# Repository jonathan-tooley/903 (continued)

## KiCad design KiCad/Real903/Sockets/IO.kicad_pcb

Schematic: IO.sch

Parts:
J3: IDC-Header_2x03_P2.54mm_Vertical
JSKT4: Circ61; MC61
JSKT4-1, JSKT4-2, JSKT4-3: IDC-Header_2x10_P2.54mm_Vertical
JSKT13: Circ19; MC19

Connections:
/Control Unit/0v: J3.5, J3.6, JSKT4.A, JSKT13.B, JSKT13.D, JSKT13.F, JSKT13.H, JSKT13.K, JSKT13.M, JSKT13.P, JSKT13.S, JSKT13.U
/Control Unit/+6v: J3.4, JSKT4.~p~
/IO/BT-30-U: JSKT4-2.17, JSKT13.N
/IO/IG1: JSKT4.~q~, JSKT4-3.1
/IO/IG2: JSKT4.~r~, JSKT4-3.2
/IO/IG3: JSKT4.~s~, JSKT4-3.3
/IO/IG4: JSKT4.~t~, JSKT4-3.4
/IO/IG5: JSKT4.~u~, JSKT4-3.5
/IO/IG6: JSKT4.~v~, JSKT4-3.6
/IO/IG7: JSKT4.~w~, JSKT4-3.7
/IO/IG8: JSKT4.~x~, JSKT4-3.8
/IO/IG9: JSKT4.~y~, JSKT4-3.9
/IO/IG10: JSKT4.~z~, JSKT4-3.10
/IO/IG11: JSKT4.AA, JSKT4-3.11
/IO/IG12: JSKT4.BB, JSKT4-3.12
/IO/IG13: JSKT4.CC, JSKT4-3.13
/IO/IG14: JSKT4.DD, JSKT4-3.14
/IO/IG15: JSKT4.EE, JSKT4-3.15
/IO/IG16: JSKT4.FF, JSKT4-3.16
/IO/IG17: JSKT4.GG, JSKT4-3.17
/IO/IG18: JSKT4.HH, JSKT4-3.18
/IO/LW-30-13: JSKT4-2.18, JSKT13.R
/IO/OA1: JSKT4.B, JSKT4-1.1
/IO/OA2: JSKT4.C, JSKT4-1.2
/IO/OA3: JSKT4.D, JSKT4-1.3
/IO/OA4: JSKT4.E, JSKT4-1.4
/IO/OA5: JSKT4.F, JSKT4-1.5
/IO/OA6: JSKT4.G, JSKT4-1.6
/IO/OA7: JSKT4.H, JSKT4-1.7
/IO/OA8: JSKT4.J, JSKT4-1.8
/IO/OA9: JSKT4.K, JSKT4-1.9
/IO/OA10: JSKT4.L, JSKT4-1.10
/IO/OA11: JSKT4.M, JSKT4-1.11
/IO/OA12: JSKT4.N, JSKT4-1.12
/IO/OA13: JSKT4.P, JSKT4-1.13
/IO/OA14: JSKT4.R, JSKT4-1.14
/IO/OA15: JSKT4.S, JSKT4-1.15
/IO/OA16: JSKT4.T, JSKT4-1.16
/IO/OA17: JSKT4.U, JSKT4-1.17
/IO/OA18: JSKT4.V, JSKT4-1.18
/IO/OS1: JSKT4.W, JSKT4-1.19
/IO/OS2: JSKT4.X, JSKT4-1.20
/IO/OS3: JSKT4.Y, JSKT4-2.1
/IO/OS4: JSKT4.Z, JSKT4-2.2
/IO/OS5: JSKT4.~a~, JSKT4-2.3
/IO/OS6: JSKT4.~b~, JSKT4-2.4
/IO/OS7~: JSKT4.~c~, JSKT4-2.5
/IO/OS8: JSKT4.~d~, JSKT4-2.6
/IO/OS9: JSKT4.~e~, JSKT4-2.7
/IO/OS10: JSKT4.~f~, JSKT4-2.8
/IO/OS11: JSKT4.~g~, JSKT4-2.9
/IO/PI1-29-AE: JSKT4-2.11, JSKT13.A
/IO/PI2-29-AF: JSKT4-2.12, JSKT13.C
/IO/PI3-29-AH: JSKT4-2.13, JSKT13.E
/IO/PR-30-E: JSKT4-2.16, JSKT13.L
/IO/PUNCH-INT: J3.3, JSKT13.T
/IO/RDR-INT: J3.1, JSKT13.V
/IO/RESET-32-20: JSKT4.PP, JSKT4-3.20
/IO/SIP-30-21: JSKT4-2.15, JSKT13.J
/IO/SOP-30-20: JSKT4-2.14, JSKT13.G
GND: J3.2, JSKT4.LL

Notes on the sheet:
Input/Output Control
Input/Output Data
OA Data
IG Data
OS Data
BP3

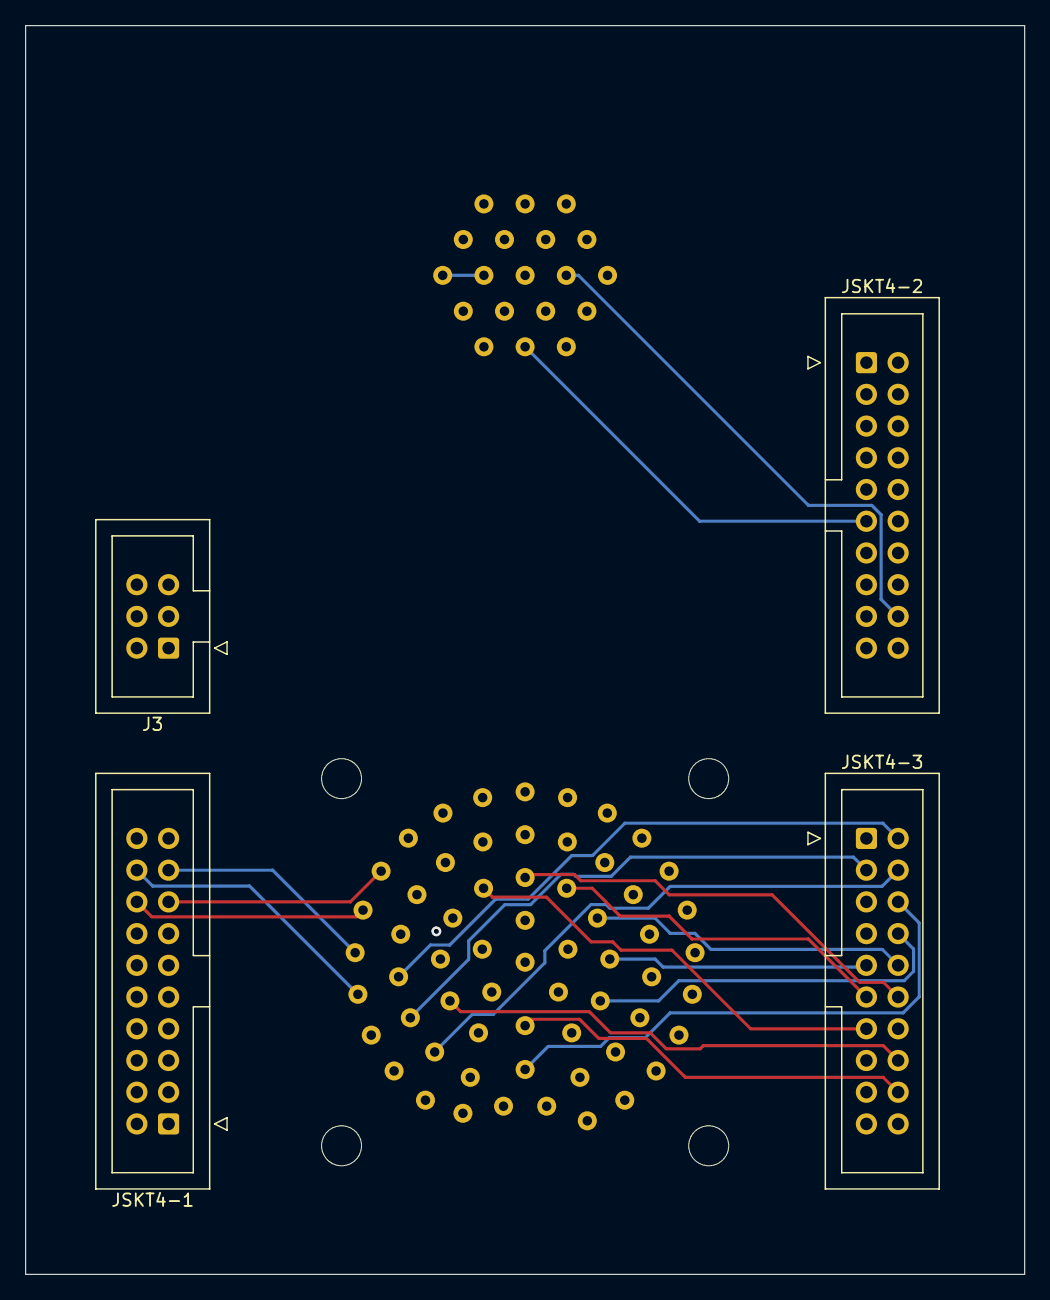
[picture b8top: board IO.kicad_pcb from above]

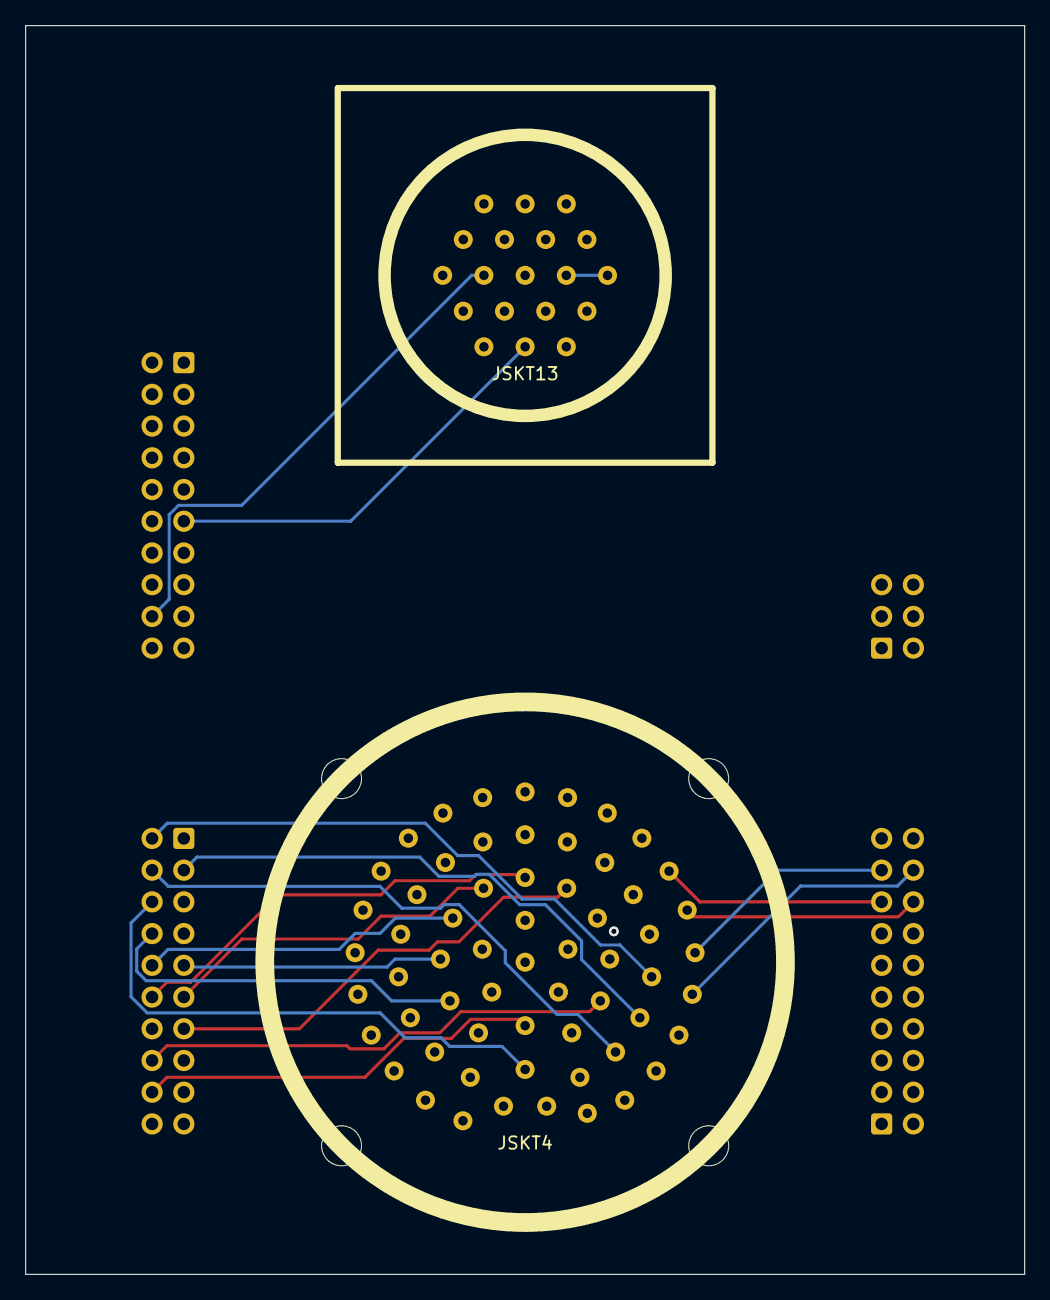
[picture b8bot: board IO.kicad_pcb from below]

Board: 4 copper layers, 80.0 x 100.0 mm, 6 parts (2 on the bottom side), 61 nets.

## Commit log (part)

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2017-02-05 Set up the project on Monodevelop
2017-02-08 Test
2017-04-22 23 April
2017-04-29 Start work on building console
2017-04-30 Added U2 input handling
2017-05-10 Removed gui file
2017-05-10 Fix to get the TTY input working
2017-05-10 Added address comments to legible
2017-05-10 Change names after creating mcp module
2017-05-14 Remove Tracing functions
2017-05-14 Improve display of the word generator
2017-05-14 Add definitions for MCP23008
2017-05-14 Remove tracing from command structures
2017-05-14 Simplify the attach command so we now only accept AT
2017-05-14 Tidy
2017-05-14 Set up control panel fuctions
2017-05-14 Add to gitignore
2017-05-20 Tie in the interrupt controls and single stepping
2017-06-11 Run with one wiring library
2017-06-11 Chang generic system
2017-06-14 Git Ignore
2017-06-14 Link 15 6144 to the physical punch
2017-06-15 Remove legible code. Now available in SIR
2017-06-15 .gitignore
2017-06-15 Further removed code relating to LP, Cards and Mag Tape
2017-06-15 Take out generic machine description as we will simulate just one machine
2017-06-15 Take out machine dependent code
2017-06-15 Simplify console commands and remove the ability to read commands from a file
2017-06-17 Change the obey to run under the processor thread and also allow us to reset from a held punch command. Start working on a holdup indicator.
2017-08-06 Return to the inline display of registers
2017-08-06 Tidy the welcome message
2017-08-06 Revert "Core store and restore, Removed tape modes, Started to clean telecodes"
    This reverts commit 739f7db2d01a4aaca170835f80c1caf80c9e96c5.
2017-08-08 Tidy the control board manufacturing files to a new folder
2017-08-08 Add CPU circuit and pcb board
2017-08-08 Add a display schematic, put cpu manufacturing files in a directory and tidy the control panel design
2017-08-13 Char.900
2017-08-14 Update the pin numbers to suit the new circuit board design
2017-08-14 Remove the console messages when controls are moved and simplify the selection of display mode or console mode.
2017-08-14 Add a simple sleep to slow day simulated tape reads
2017-08-14 Remove the old teleprinter routines
2017-08-14 Remove the old timing mechanism
2017-08-16 Circuit design updates
2017-08-19 Remove the memory and models modules from the project by merging with other items
2017-08-19 Remove dump as sir functionality
2017-08-19 Tidy exceptions
2017-08-19 Correct bug in the display code
2017-08-19 Stop using the off light to show holdups
2017-08-21 Finalise display board
2017-09-24 Include code to initialise the multiplexer and select the control panel bus prior to setting up the control panel chips
2017-09-24 Add some test code to flash the accumulator to the display unit
2017-09-24 Before we update the control panel and scan its switches we switch to the control panel bus
2017-09-24 Remove ACD telecode and tape modes
2017-10-16 Remove txt telecode option
2017-10-16 Remove the reverse command
2017-10-18 Link more LEDs into the display panel
2017-10-22 Remove the SIR Helper routines
2017-10-22 Remove unwanted functions
2017-10-24 Change display to show the old SCR to remove the annoying jitter on infinite loop stops
2017-10-24 Simplify read modes, punch modes and telecodes
2017-10-28 Link the on and off switches to the relay and fan
2017-11-05 Correct the MCP addresses
2017-11-12 Take out any threading references in Devices
2017-11-12 Take out the Module code
2017-11-12 Change the code to no longer use threading
2017-11-18 Put a timeout in the teletype read process and also set a teletype demand flag
2017-11-18 Move the code to show interrupt status so that all the control panel lighting operations are in one place
2017-11-18 Move the word gen code to be with all the other input button code.
2017-11-18 Change the processor to use the panel light and panel button functions
2017-11-18 Make the off key light go off after a kill command
2017-11-18 Attempt at a ttydemand light using the x led
2017-11-18 Allow us to reset or 'off' during a held up punch operation
2017-11-18 We replace variables like alive, on, reset, stopped, obey etc. with a hierarchical status
2017-11-19 Remove the off switch code and put in its own routine
2017-11-19 Create a routine for running the next instruction from core
2017-11-19 Make Enter Switch a separate routine
2017-11-19 Make Obey a separate routine
2017-11-19 Make on a separate routine
2017-11-19 Let reset jump and word gen separate routines
2017-11-19 Split display registers so we can just update Accumulator
2017-11-19 Reference earlier modules and move the access functions to the top so other routines can access
2017-11-19 Make it faster to interrupt input holdups
2017-11-19 Remove excess code
2017-11-19 Improve the processor
2017-11-19 Start some code where we can put commands (prior to this being moved to a new interface board)
2017-11-26 Allow commands in the reset state
2017-11-26 List directory only shows .bin .900 and .rlb files
2017-11-26 We can't use writemem until after enable initial instructions
2017-11-26 Improvements to the machine script
2017-12-10 Experiment with TTY buffer
2017-12-10 Punch to a file if one is attached, else send to the physical punch
2017-12-10 New command structure and remove the test for reset from tape reads to see if we can get consistently good reads.
2018-02-11 Tidy main
2018-02-11 Interrupt Experiment
2018-02-12 Add display
2018-04-01 Try to improve tape read with interupt
2018-04-08 Put in references to globals and move some basic functions
2018-04-08 Add a wrapper for locking and unlocking functions that we may be able to use with multiplexing
2018-04-08 Add definitions for MCP interrupt control registers
2018-04-08 Add an interrupt handler to control on off and reset
2018-04-11 Change play style to notset because none is a reserved word
2018-04-11 Update playstyle
2018-04-11 Move Interrupt to a new spot
2018-04-14 Create a new file for functions that are used with the system console
2018-04-14 Make our punch code compliant with bus locking
2018-04-14 Add a console reference to main
2018-04-14 Add a reference to console
2018-04-14 Move code
2018-04-14 Clear out code that we have just improved
2018-04-14 Improve the processor loop
2018-04-14 Replace remaining bus commands with locked bus protocols
2018-04-19 Rename some wiring PI functions with long names and only keep bit and mask definitions we actually use
2018-04-21 Remove open statements that are not needed
2018-04-21 Remove telecode name. Not used.
2018-04-21 Take away the tape mode converters
2018-04-21 Make telecodeof independent of telecode as we only have one
2018-04-21 Let TranslateFromText be independent of telecode
2018-04-21 Put the type defs in Globals
2018-04-21 Simplify the calling of mcp routines
2018-04-22 simplify code with an open statement
2018-05-04 reorg kicad
2018-06-16 New CPU Design
2018-06-16 Revert "Revert "New CPU Design""
    This reverts commit a307b05540114be9f6772760b58b5b7a0b78f40f.
2018-06-16 Add footprints and gerber plot
2018-06-24 Make sure panel lights are off when we shutdown
2018-06-24 Move to Visual Studio and some kicad updates
2018-06-24 Move to Visual Studio
2018-06-26 Tidy up unused references
2018-06-26 Add a status for restarting
2018-06-26 Call the interrupt processor before starting and stopping
2018-06-26 Complete all the possible status change messages
2018-06-26 New gitignore for vs
    New git ignore for VS
2018-06-26 new gitignore
2018-06-26 Update ROOLights to include NotRunning, SwitchingOff and SwitchingOn
2018-06-26 Remove Restart Switch
2018-06-26 Add More interrupt combinations
2018-06-26 Remove the interrupt debounce
2018-06-28 Define new operating modes
2018-06-28 Make the ROOLights respond to new modes
2018-06-28 Simplify EnterSwitch
2018-06-28 Add new modes to the mode status display
2018-06-28 New version of PanelHandler
2018-07-01 For some reason this is needed to run gpio
2018-07-01 Make the TTY input completely interruptable
2018-07-01 Close work 1 July
2018-07-09 Create an edge type type for defining interrupts
2018-07-09 Comment out the interrupt test code
2018-07-09 Replace handshake read code with a wait for date handled by interrupt
2018-07-09 New interrupt code for reader
2018-07-16 Change the TTY circuit
2018-07-16 Update the TTY PCB
2018-07-16 Change TTY to run at 30 CPS which is more natural for the TTY43
2018-07-22 New metal panels for the tape drive
2018-07-22 New board has slightly different addressing
2018-07-22 Move blocks from machine to globals and devices
2018-07-22 Remove test print of value from reader
2018-08-05 Simplify the dll imports
2018-08-05 Change the way we call wiringpisetup
2018-08-05 Add locking for the IO Controller
2018-08-05 Increade the port buffers and set the newline
2018-08-05 Setup all the pins and interrupts for the IO Control
2018-08-05 Add functions to serve the IO Control interrupts
2018-08-05 Tidy the panel handler
2018-08-05 Adjust the CPU board
2018-08-05 Change the directory listing to run on the TTY
2018-08-05 Add an enumerated type for IO operations
2018-08-05 Add interrupt and operation statuses
2018-08-05 Add interrupt operations into the main processor loop
2018-08-05 Improvements to PCBs and footprints
2018-08-05 New Front Panel for the tape drive
2018-08-05 VS Changes
2018-08-05 Simplify the old order stop control
2018-08-05 Add logic to drive the IO control buttons
2018-10-11 Produce a new Gerber for In Out Control board
2018-10-11 Introduce a tapeloaded variable
2018-10-11 Add extra variables for the in out rotarty switches
2018-10-11 New IO board uses different pins
2018-10-11 Fault with punch port so remap to plotter
2018-10-11 New IO board has new pin definitions
2018-10-11 New IO Board PCB design
2018-10-11 Turn off reader attached light at end of tape
2018-10-11 Change punch code to use plotter port
2018-10-11 Control IO Board lights
2018-10-11 Allow us to select utilities directory
2018-10-16 Shorten the name of the SCR
2018-10-16 Add some comments to global variables
2018-10-16 Move the MessagePut function from Globals and give tty option
2018-10-16 Put in the code for IO interrupt decoding.
    Test for a button before we just accept the rotary switch
2018-10-16 Try and clear the panel interrupt as soon as detected
2018-10-16 When we turn on we set the two detached lights on
2018-10-16 Set up IO interrupt actions
2018-10-16 Move MCP int clear variables to Global
2018-10-16 Combine open reader functions
2018-10-16 Wrap long comment
2018-10-16 Remove the distinction for NotRunning and Stopped
2018-10-18 Name change to ReadTTYchar
2018-10-18 Tidy the input routines
2018-10-18 Remove the AGet function
2018-10-18 Remove WGet function
2018-10-18 Remove OldSGet function
2018-10-18 Remove interrupt level functions
2018-10-18 Remove WPut
2018-10-20 Remove pin types that we don't need
2018-10-20 Remove ttyDemand
2018-10-20 Prepare to test that the mechanical punch is on
2018-10-20 Change interrupt messaging
2018-10-20 Activate interrupt on the control panel buttons for Trace, Online, Manual and Trigger Int
2018-10-20 Replace the Panel Buttons function with interrupt code
2018-10-21 Add a stop option to the Active Reader
2018-10-21 Send Interrupt Trigger Messages
2018-10-21 When we reset make sure the various holdup and demand lights are off
2018-10-21 Add control code to respond when Read or Stop are pressed
2018-10-21 Adjust the punch write so that if the punch does not respond it flips the device back to detached status
2018-10-21 Stop tracking .suo
2019-04-29 Update for PCB Design
2019-08-30 G Board
2019-08-30 Update Gerbers
2019-09-01 New Frontpanels
2019-09-22 New boards
2019-10-23 23 oct
2020-07-05 July backplane update
2020-08-02 August 2
2020-08-15 August 15
2020-10-02 Finalise KT88 and add Quad to original design
2023-02-10 New Backplanes
2023-02-11 Auto stash before merge of "master" and "origin/master"
2023-02-11 BP2 and 3
2023-02-17 Cleanup from v5 files
